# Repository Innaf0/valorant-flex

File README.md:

# valorant-flex
I made Tianyan (天眼) inspired by an actual valorant flex named Statcom. With Tianyan you can check your K/D/A, on which map is your win rate the highest,which agent you use the most,your rank etc. you can even play music on it!
This project came into existence bc I was lowk obsessed with valo :D

## Assembly steps:
1. get your PCB and put all your components on it
2. print the shell and the buttons
3. melt the heat set inserts into the frontshell
4. assemble everything together and tighten with screws
5. flash the firmware
 and you're done:D !!!
## 3D models :)
Here's the front side of my 3D model with valo art!!

and here's the backside with valo art again:)

## PCB with and without components!

Here's the front of my PCB w components:

Here's the back of my PCB w components

AND here's my PCB without components so you can see the art!!

## Schematic:3

Here's my schematic just incase lmao

## ZINE page(pdf.)

Here's my ZINE<3

## BOM ;)

Here's my BOM!!
| item:              | price per unit: | quantity:    | total price: | link:                                                 |
|--------------------|-----------------|--------------|--------------|-------------------------------------------------------|
| Display            | $10.52          | 1            | $10.52       | https://www.aliexpress.com/item/1005005334824151.html |
| Pi pico2           | $13.20          | 1            | $13.20       | https://www.aliexpress.com/item/1005009845096943.html |
| DAC                | $4.95           | 1            | $4.95        | https://www.adafruit.com/product/6250                 |
| Speaker            | $3.61           | 1            | $3.61        | https://www.aliexpress.com/item/1005005701427186.html |
| button             | $0.0182         | 1            | $0.0182      | https://www.aliexpress.com/item/1005007623070623.html |
| right-angle button | $0.0895         | 2            | $0.179       | https://www.aliexpress.com/item/1005006149378588.html |
| battery holder     | $0.68           | 1            | $0.68        | https://www.aliexpress.com/item/1005008468643124.html |
| PCB                | $0.40           | 1            | $0.40        | https://cart.jlcpcb.com                               |
| screws             | $0.077          | 3            | $0.230       | https://www.aliexpress.com/item/1005007264845313.html |
| heat set insert    | $0.070          | 3            | $0.209       | https://www.aliexpress.com/item/1005006798286851.html |
|                    |                 | total price: | $34.00       |                                                       |

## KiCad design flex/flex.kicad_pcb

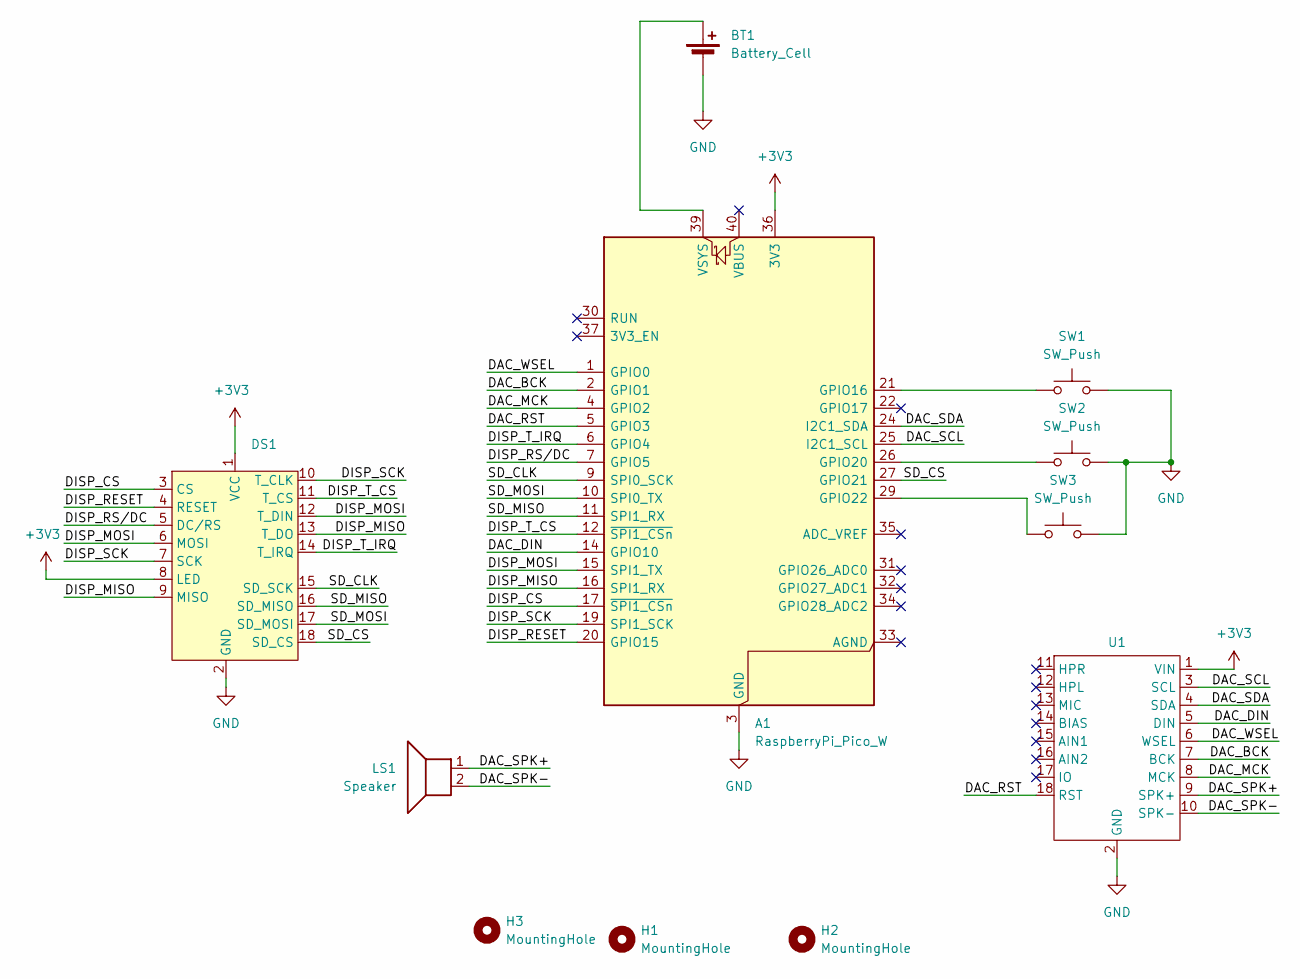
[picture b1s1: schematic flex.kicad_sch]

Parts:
A1: RaspberryPi_Pico_W; RaspberryPi_Pico_Common_THT
BT1: Battery_Cell; PinHeader_1x02_P2.54mm_Vertical
DS1: Display
H1, H2, H3: MountingHole; MountingHole_2.2mm_M2
LS1: Speaker; PinHeader_1x02_P2.54mm_Vertical
SW1: SW_Push; SW-TH_4P-L4.5-W4.5-P3.00-LS4.8
SW2, SW3: SW_Push; SW_SPST_Omron_B3F-315x_Angled
U1: DAC

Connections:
+3V3: A1.36 (3V3), DS1.1 (VCC), DS1.8 (LED), U1.1 (VIN)
/DAC_BCK: A1.2 (GPIO1), U1.7 (BCK)
/DAC_DIN: A1.14 (GPIO10), U1.5 (DIN)
/DAC_MCK: A1.4 (GPIO2), U1.8 (MCK)
/DAC_RST: A1.5 (GPIO3), U1.18 (RST)
/DAC_SCL: A1.25 (I2C1_SCL), U1.3 (SCL)
/DAC_SDA: A1.24 (I2C1_SDA), U1.4 (SDA)
/DAC_SPK+: LS1.1, U1.9 (SPK+)
/DAC_SPK-: LS1.2, U1.10 (SPK-)
/DAC_WSEL: A1.1 (GPIO0), U1.6 (WSEL)
/DISP_CS: A1.17 (~SPI1_CSn), DS1.3 (CS)
/DISP_MISO: A1.16 (SPI1_RX), DS1.9 (MISO), DS1.13 (T_DO)
/DISP_MOSI: A1.15 (SPI1_TX), DS1.6 (MOSI), DS1.12 (T_DIN)
/DISP_RESET: A1.20 (GPIO15), DS1.4 (RESET)
/DISP_RS/DC: A1.7 (GPIO5), DS1.5 (DC/RS)
/DISP_SCK: A1.19 (SPI1_SCK), DS1.7 (SCK), DS1.10 (T_CLK)
/DISP_T_CS: A1.12 (~SPI1_CSn), DS1.11 (T_CS)
/DISP_T_IRQ: A1.6 (GPIO4), DS1.14 (T_IRQ)
/SD_CLK: A1.9 (SPI0_SCK), DS1.15 (SD_SCK)
/SD_CS: A1.27 (GPIO21), DS1.18 (SD_CS)
/SD_MISO: A1.11 (SPI1_RX), DS1.16 (SD_MISO)
/SD_MOSI: A1.10 (SPI0_TX), DS1.17 (SD_MOSI)
GND: A1.3 (GND), A1.8 (GND), A1.13 (GND), A1.18 (GND), A1.23 (GND), A1.28 (GND), A1.38 (GND), BT1.2 (-), DS1.2 (GND), SW1.2, SW2.2, SW3.2, U1.2 (GND)
unnamed: A1.21 (GPIO16), SW1.1
unnamed: A1.26 (GPIO20), SW2.1
unnamed: A1.29 (GPIO22), SW3.1
unnamed: A1.39 (VSYS), BT1.1 (+)

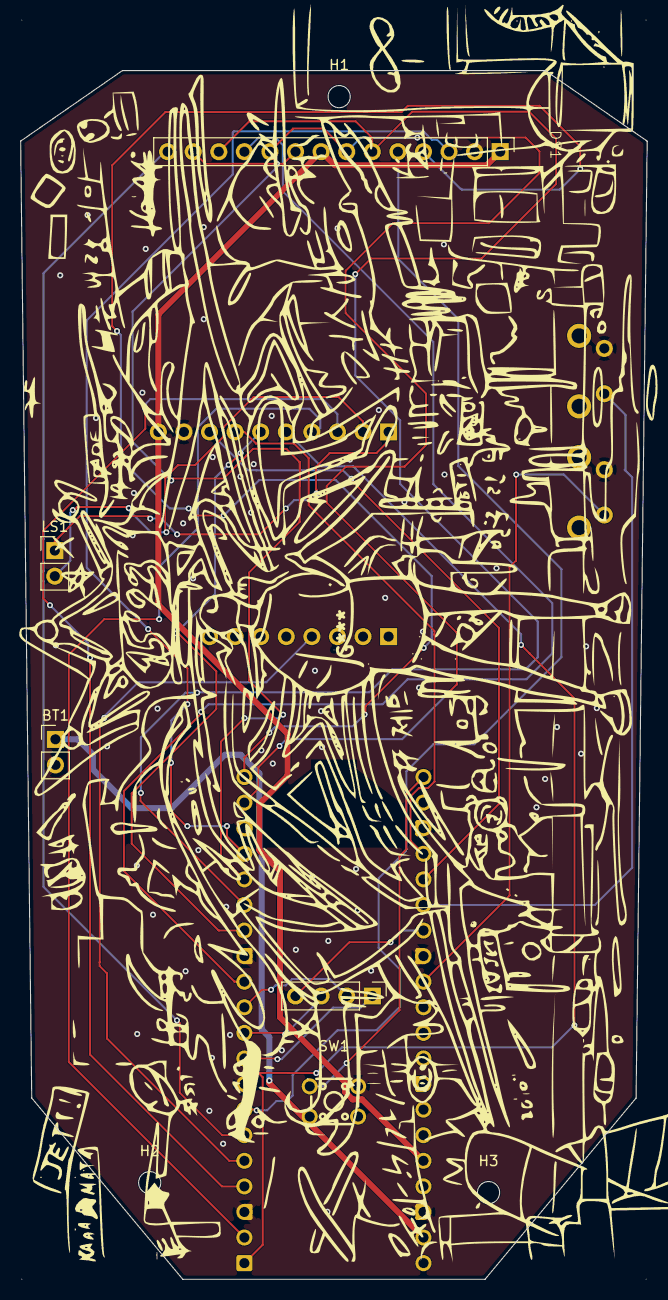
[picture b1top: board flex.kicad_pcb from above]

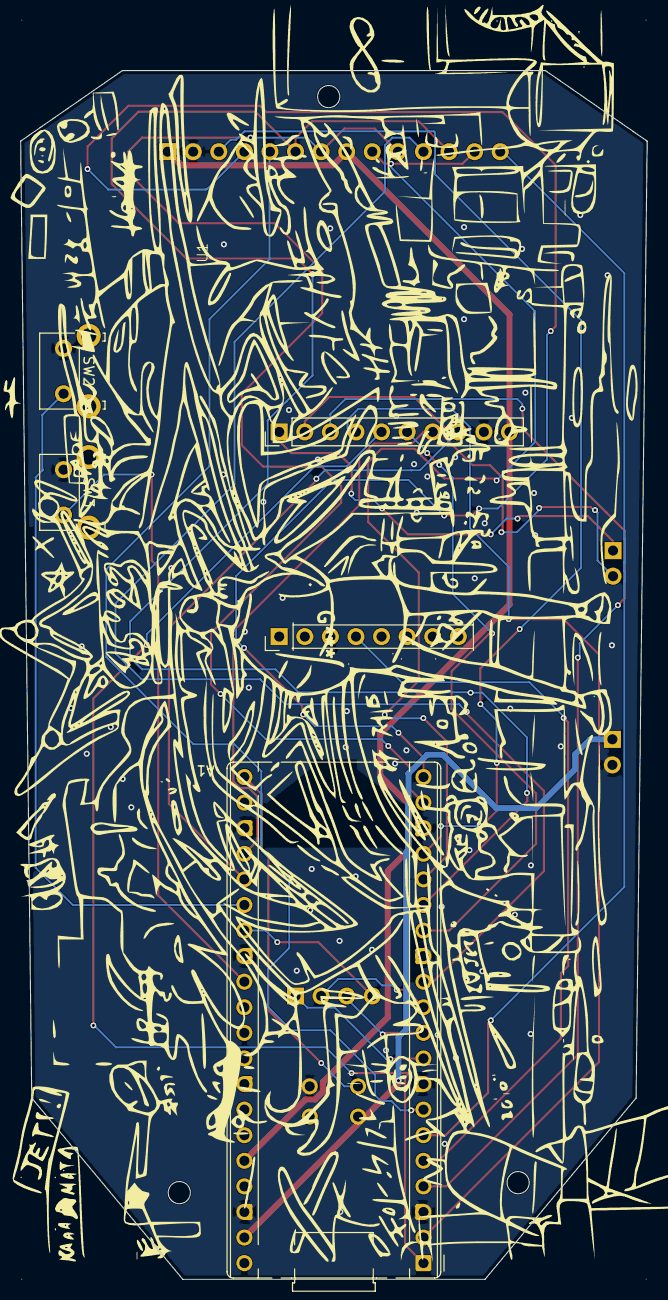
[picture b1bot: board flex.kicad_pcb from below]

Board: 2 copper layers, 62.2 x 125.0 mm, 11 parts (4 on the bottom side), 27 nets.

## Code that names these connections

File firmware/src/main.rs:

#![no_std]
#![no_main]
mod audio;
mod display;
mod irqs;
mod request;
mod sd_card;
mod touch;

use core::cell::RefCell;

use defmt::*;
use embassy_executor::Spawner;
use embassy_rp::gpio::{Input, Level, Output, Pull};
use embassy_rp::peripherals::SPI1;
use embassy_rp::pio::Pio;
use embassy_rp::spi::{Blocking, Spi};
use embassy_time::{Duration, Timer};
use embedded_hal_bus::spi::{NoDelay, RefCellDevice};
use static_cell::StaticCell;
use {defmt_rtt as _, panic_probe as _};

use crate::irqs::Irqs;

#[embassy_executor::main]
async fn main(spawner: Spawner) {
    let p = embassy_rp::init(Default::default());

    // ── SD card on SPI0 ──────────────────────────────────────
    let mut sd_handle = sd_card::init_sd_card(
        p.SPI0,   // SPI peripheral
        p.PIN_6,  // SCK  (SD_CLK / SPI0 SCK)
        p.PIN_7,  // MOSI (SD_MOSI / SPI0 TX)
        p.PIN_4,  // MISO (SD_MISO / SPI0 RX)
        p.PIN_21, // CS   (SD_CS)
    );
    let config = sd_handle.read_config();

    // ─ WiFi (CYW43) ─────────────────────────────────────────
    let ctx = request::init_network(
        spawner,
        config.wifi_ssid.as_str(),
        config.wifi_password.as_str(),
        config.api_key.as_str(),
        config.player_region.as_str(),
        config.player_name.as_str(),
        config.player_tag.as_str(),
        p.PIN_23,
        p.PIN_25,
        p.PIN_24,
        p.PIN_29,
        p.PIO0,
        p.DMA_CH0,
    )
    .await;

    // ── Shared SPI1 bus for display + touch ─────────────────
    let mut spi_config = embassy_rp::spi::Config::default();
    spi_config.frequency = 64_000_000;

    let spi_bus = Spi::new_blocking(
        p.SPI1, p.PIN_14, // SCK  (DISP_SCK / DISP_T_CLK)
        p.PIN_11, // MOSI (DISP_MOSI / DISP_T_MOSI)
        p.PIN_12, // MISO (DISP_MISO / DISP_T_DO)
        spi_config,
    );

    static SPI_BUS: StaticCell<RefCell<Spi<'static, SPI1, Blocking>>> = StaticCell::new();
    let spi_bus = SPI_BUS.init(RefCell::new(spi_bus));

    // Display CS: GPIO13, Touch CS: GPIO9, Touch IRQ: GPIO8
    let display_spi = RefCellDevice::new(spi_bus, Output::new(p.PIN_13, Level::High), NoDelay);
    let touch_spi = RefCellDevice::new(spi_bus, Output::new(p.PIN_9, Level::High), NoDelay);

    // ── ILI9341 display ─────────────────────────────────────
    let mut display = display::init_display(
        display_spi,
        p.PIN_5,  // DC   (DISP_RS/DC)
        p.PIN_15, // RST  (DISP_RESET)
    );

    // ── Touch controller (shares SPI1 with display) ──────────
    let mut touch = touch::Touch::new(touch_spi, p.PIN_8); // IRQ  (DISP_T_IRQ)

    // ── I2S audio player on PIO1 ─────────────────────────────
    const SAMPLE_RATE: u32 = 48_000;
    const BIT_DEPTH: u32 = 16;

    let Pio {
        mut common, sm0, ..
    } = Pio::new(p.PIO1, Irqs);

    let mut player = audio::I2sPlayer::new(
        &mut common,
        sm0,
        p.DMA_CH4,
        Irqs,
        p.PIN_10, // DIN  (DAC_DIN)
        p.PIN_1,  // BCK  (DAC_BCK)
        p.PIN_0,  // WSEL (DAC_WSEL)
        SAMPLE_RATE,
        BIT_DEPTH,
    );

    // ── Buttons (active low) ─────────────────────────────────
    let play_button = Input::new(p.PIN_16, Pull::Up); // SW1
    let _btn2 = Input::new(p.PIN_20, Pull::Up); // SW2
    let _btn3 = Input::new(p.PIN_22, Pull::Up); // SW3

    info!(
        "Ready. Press SW1 (GPIO16) to play AUDIO.WAV ({} Hz / {}-bit).",
        SAMPLE_RATE, BIT_DEPTH
    );

    loop {
        // Check for button press
        if play_button.is_low() {
            info!("Button pressed – playing AUDIO.WAV ...");

            let result = player.play_wav(&mut sd_handle, "AUDIO.WAV").await;

            match result {
                Ok(()) => info!("Playback finished successfully."),
                Err(e) => warn!("Playback error: {:?}", e),
            }

            // Wait for button release to avoid retriggering
            while play_button.is_low() {
                Timer::after(Duration::from_millis(20)).await;
            }
            info!("Button released.");
        }

        // ── Check for touch input ────────────────────────────
        if touch.is_touched() {
            if let Some((x, y)) = touch.read() {
                info!("Touch at ({}, {})", x, y);
            }
        }

        // ── Fetch latest match and update display ────────────
        match request::fetch_match(&ctx).await {
            Some(m) => {
                info!("=== Match ===");
                info!("Map:         {}", m.map.as_str());
                info!("Mode:        {}", m.mode.as_str());
                info!("Region:      {}", m.region.as_str());
                info!("Started:     {}", m.game_start.as_str());
                info!("Rounds:      {}", m.rounds_played);
                info!(
                    "Score:       Red {} - {} Blue",
                    m.red_rounds_won, m.blue_rounds_won,
                );
                info!(
                    "Winner:      {}",
                    if m.red_has_won { "Red" } else { "Blue" }
                );

                info!("=== Players ===");
                for player in &m.players {
                    info!(
                        "  [{}] {} #{} | {} | {} | K/D/A: {}/{}/{} | HS: {}",
                        player.team.as_str(),
                        player.name.as_str(),
                        player.tag.as_str(),
                        player.character.as_str(),
                        player.rank.as_str(),
                        player.kills,
                        player.deaths,
                        player.assists,
                        player.headshots,
                    );
                }

                // Draw the match on the display
                display::draw_match(&mut display, &m);
            }
            None => {
                warn!("Failed to fetch match data, retrying...");
            }
        }

        Timer::after(Duration::from_secs(30)).await;
    }
}

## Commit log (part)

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2026-04-05 started working on the schematic
2026-06-13 added 3d models and moved buttons and edge
2026-06-19 started on firmware
2026-06-19 added images to README
2026-06-20 added firmware and art
2026-06-20 rendered and coded firmware
2026-06-20 did some firmware did my zine and my BOM
2026-06-20 Enhance README with project details and images
    Updated README to include project description, images, and BOM.
2026-06-20 added cad files, and renders
2026-06-20 updated BOM
2026-06-20 Enhance README with assembly and BOM information
    Added assembly steps, 3D models, PCB images, schematic, ZINE page, and BOM details.
